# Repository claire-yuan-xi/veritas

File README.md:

# Veritas: A Pill Screener
Veritas is a small owl-shaped pill screener that uses water dissolution and light sensing to check whether an over-the-counter pill matches what the pill's label says.

To use Veritas, first you take a small glass vial of water that is provided alongside Veritas, and then drop the pill inside. Then, you shake the vial for 10 seconds, and then set the vial back inside the owl. If you forget how to do any of these steps, fret not! The OLED screen will walk you through the process. 

Inside, Veritas will first shine five colors of LED (red, green, blue, infrared, and ultraviolet) through the dissolving pill, in that order. Then, a light sensor inside will measure how much of each color makes it through the dissolved pill. These five numbers are the main data points Veritas will send to the mobile app over Bluetooth, which will then start a process of the app comparing the scan of the pill with the known data points of that pill. The mobile app will then send the readings back to the OLED screen, which will then output the result (Math, Doesn't Match, or Inconclusive).
## Why I made Veritas
The WHO estimates that 1 in 10 medical products in low and middle income countries is substandard or falsified. Given the current state of the US' healthcare system, most people have low access to proper lab tests, and when they do, they're often expensive and slow. Most people have no way to check a pill at home.

Owls are known for being wise, which inspired the design of Veritas. Moreover, truth in Latin (and partially Yale's latin motto) inspired the name "Veritas." 

Also, special thanks to my marketing teacher and the friends who helped in the design of Veritas' flyer! Also my access to the school's Adobe Premiere Suite <3

## Features

+ 5 Colors of light shined: red, green, blue, 940 nm infrared, and 400 nm UV
+ TSL2591 high sensitivity light sensor
+ 0.96" OLED screen
+ Seeed XIAO ESP32-S3 with Bluetooth Low Energy 
+ Custom 50 x 40 mm PCB
+ 3D printed 110 mm owl case 
+ USB-C Connection

## Case

The case is a 110 mm sphere with a flat bottom designed in Autodesk Fusion. The case breaks down into 3 parts: 

+ the body with the PCB at the bottom, the cutout for the OLED, the beak, wings, chest feathers, and feet.
+ the chamber for the vial to stand, right above the LEDs, which fits standard sized glass vials (approx. 27 x 60 mm)
+ the roof/sensor cap where the TSL2591 sensor is mounted

The parts are held together with heat-set inserts, to which Im printing in black PLA so as to not let any light in and interfere with the readings.

## PCB

Using KiCad, the PCB ended up being about 50 x 40 mm. The XIAO ESP32-S3 plugs into two 7 pin headers so it can be swapped out whenever. The five LEDs sit in a column under the chamber so their light goes straight up the vial to the sensor. Each LED has its own current-limiting resistor to which the light sensor and the OLED connect with 4 pin headers. 

There's also a spot for a small transistor and diode that could drive a stirring fan, which was left unpopulated for the purposes of Veritas as I found shaking the glass vial by hand works fine. 
The gerbers are in pcb/veritas/gerbers.zip and can be ordered from JLCPCB.

## Schematic

## Firmware
The firmware is in firmware/veritas/veritas.ino and was written in Arduino's desktop IDE. The code essentially covers the commands for the OLED screen display and the Bluetooth connection to the mobile app. 

### Libraries used: 

+ Adafruit TSL2591 library 
+ Adafruit unified sensor 
+ Adafruit SSD1306
+ Adafruit GFX library 
+ ESP32 BLE

## App

The mobile (iPhone) app is written in Swift with SwiftUI (in 'app/'). The app connects Veritas over Bluetooth, starts scans, saves reference scans of the actual, known pills, and compares new scans against them to decide Match, Doesn't Match, or Inconclusive. The app is still a work in progress, which will be finished in tandem with the hardware portion of Veritas.

## Bill of Materials

See [BOM.csv](BOM.csv) for the full list of parts with links and prices. 

## Credits

Component footprints and 3D models are from the standard KiCAD libraries. The XIAO ESP32-S3 model in the renders is a placeholder. 

Libraries by Adafruit(TSL2591, SSD1306, GFX) and Espressif (ESP32 BLE).

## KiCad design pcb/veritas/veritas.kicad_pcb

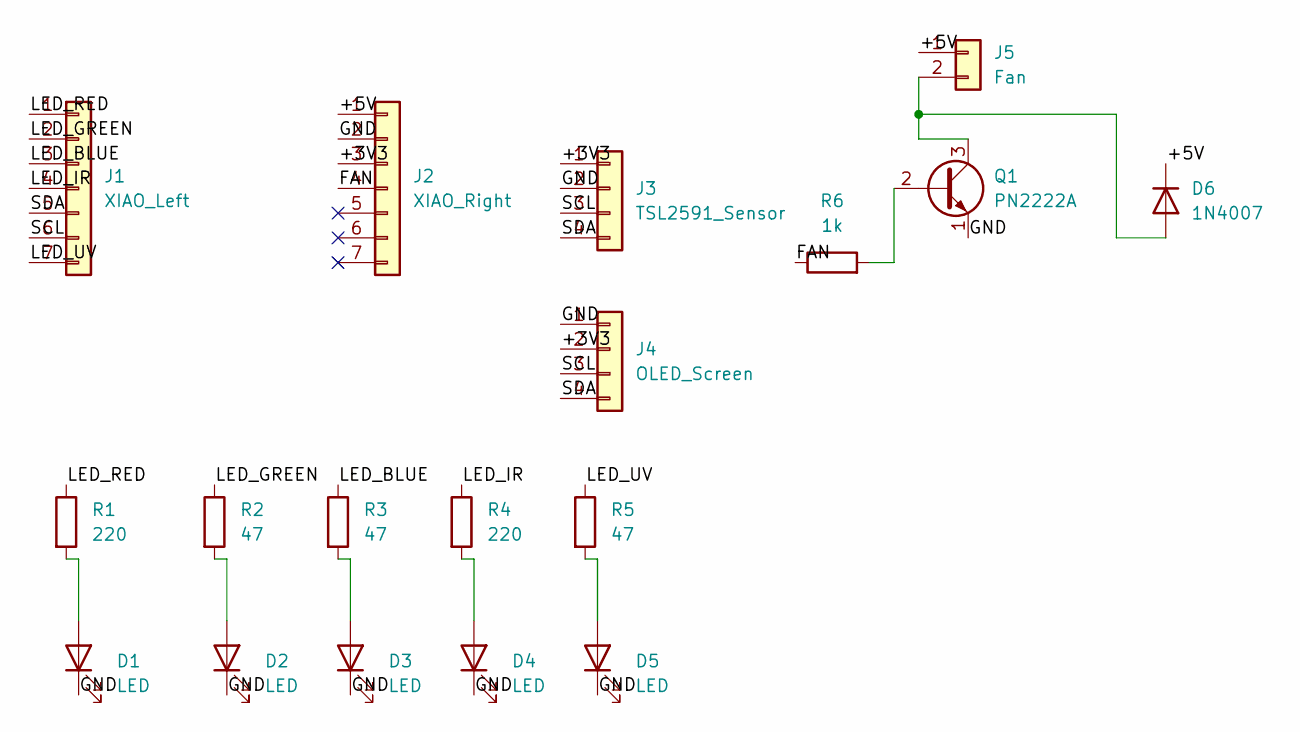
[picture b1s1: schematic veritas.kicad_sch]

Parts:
D1, D2, D3, D4, D5: LED; LED_D5.0mm
D6: 1N4007; D_DO-41_SOD81_P10.16mm_Horizontal
J1: XIAO_Left; PinSocket_1x07_P2.54mm_Vertical
J2: XIAO_Right; PinSocket_1x07_P2.54mm_Vertical
J3: TSL2591_Sensor; PinHeader_1x04_P2.54mm_Vertical
J4: OLED_Screen; PinHeader_1x04_P2.54mm_Vertical
J5: Fan; PinHeader_1x02_P2.54mm_Vertical
Q1: PN2222A; TO-92_Inline
R1, R4: 220; R_Axial_DIN0207_L6.3mm_D2.5mm_P10.16mm_Horizontal
R2, R3, R5: 47; R_Axial_DIN0207_L6.3mm_D2.5mm_P10.16mm_Horizontal
R6: 1k; R_Axial_DIN0207_L6.3mm_D2.5mm_P10.16mm_Horizontal

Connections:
/+3V3: J2.3, J3.1, J4.2
/+5V: D6.1 (K), J2.1, J5.1
/FAN: J2.4, R6.1
/GND: D1.1 (K), D2.1 (K), D3.1 (K), D4.1 (K), D5.1 (K), J2.2, J3.2, J4.1, Q1.1 (E)
/LED_BLUE: J1.3, R3.1
/LED_GREEN: J1.2, R2.1
/LED_IR: J1.4, R4.1
/LED_RED: J1.1, R1.1
/LED_UV: J1.7, R5.1
/SCL: J1.6, J3.3, J4.3
/SDA: J1.5, J3.4, J4.4
unnamed: D1.2 (A), R1.2
unnamed: D2.2 (A), R2.2
unnamed: D3.2 (A), R3.2
unnamed: D4.2 (A), R4.2
unnamed: D5.2 (A), R5.2
unnamed: D6.2 (A), J5.2, Q1.3 (C)
unnamed: Q1.2 (B), R6.2

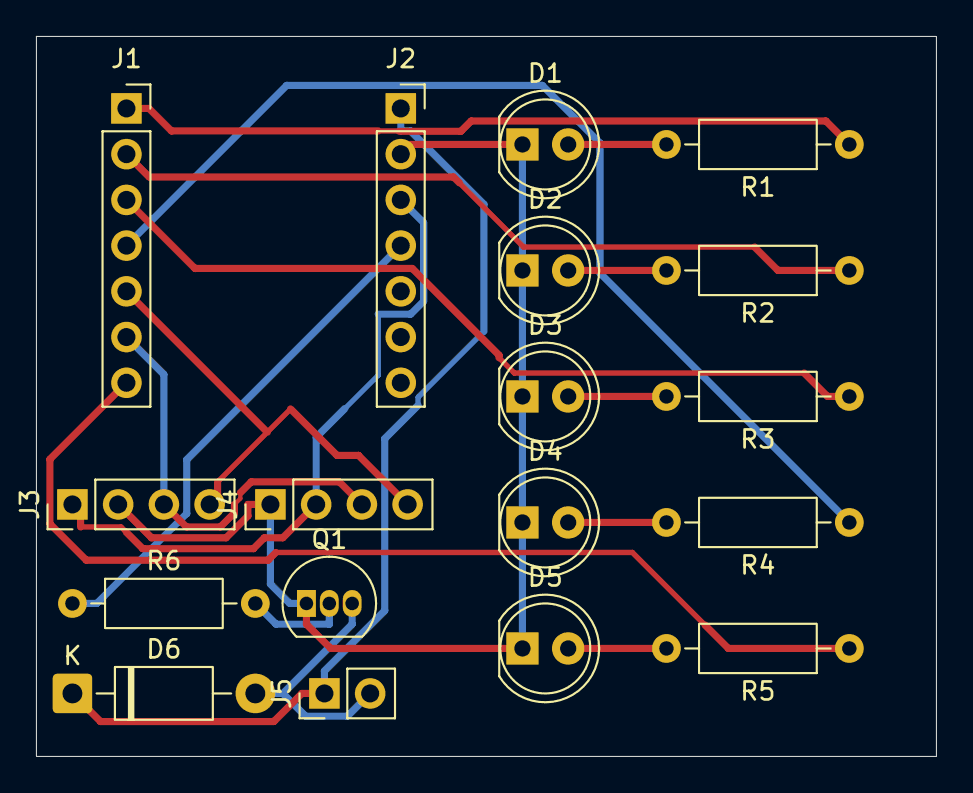
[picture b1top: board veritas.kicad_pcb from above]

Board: 2 copper layers, 50.0 x 40.0 mm, 18 parts (0 on the bottom side), 18 nets.

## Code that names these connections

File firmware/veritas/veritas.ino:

#include <Wire.h>
#include <Adafruit_Sensor.h>
#include <Adafruit_TSL2591.h>
#include <Adafruit_GFX.h>
#include <Adafruit_SSD1306.h>
#include <BLEDevice.h>
#include <BLEServer.h>
#include <BLE2902.h>

// firmware for the Seeed XIAO ESP32-S3

// LED pins (one LED per color of light)
const int LED_RED = D0;
const int LED_GREEN = D1;
const int LED_BLUE = D2;
const int LED_IR = D3;
const int LED_UV = D6;

// fan pin
const int FAN_PIN = D10;

// all LEDs in the order their flashed
const int LEDS[] = {LED_RED, LED_GREEN, LED_BLUE, LED_IR, LED_UV};
const char* LED_NAMES[] = {"red", "green", "blue", "ir", "uv"};
const int NUM_LEDS = 5;

//this is the light sensor above the vial
Adafruit_TSL2591 tsl = Adafruit_TSL2591(2591);

// one reading per LED
uint16_t readings [NUM_LEDS];

// the OLED screen (128 x 64 pixels) i.e. the owls face
Adafruit_SSD1306 display(128, 64, &Wire, -1);

// owl moods (how the eyes look)
const int AWAKE = 0;
const int SLEEPY = 1;
const int HAPPY = 2;
const int WORRIED = 3;
const int UNSURE = 4;
const int BROKEN = 5;
const int LOOK_DOWN = 6;

// where the eyes sit on the screen
const int EYE_L = 36;
const int EYE_R = 92;
const int EYE_Y = 24;
const int EYE_SIZE = 16;

// draws one eye at x in the given mood
void drawEye(int x, int mood) {
  if (mood == BROKEN) {
    // X eye
    for (int t = 0; t< 2; t++) {
      display.drawLine(x-10 + t, EYE_Y - 10, x +10 + t, EYE_Y + 10, SSD1306_WHITE);
      display.drawLine(x-10+t, EYE_Y +10, x+10+t, EYE_Y -10, SSD1306_WHITE);
    }
    return;
  }

  if (mood == HAPPY) {
    // ^ shape: a white circle with a black circle covering its bottom
    display.fillCircle(x, EYE_Y + 4, EYE_SIZE, SSD1306_WHITE);
    display.fillCircle(x, EYE_Y + 12, EYE_SIZE, SSD1306_BLACK);
    return;
  }

  // normal eye: white circle + black pupil
  display.fillCircle(x, EYE_Y, EYE_SIZE, SSD1306_WHITE);
  int pupilY = EYE_Y;
  if (mood == LOOK_DOWN) {
    pupilY = EYE_Y + 7;
  }
  display.fillCircle(x, pupilY, 6, SSD1306_BLACK);

  if (mood == SLEEPY) {
    // eyelid: black box over the top half of the eye
    display.fillRect(x - EYE_SIZE, EYE_Y - EYE_SIZE, EYE_SIZE * 2 + 1, EYE_SIZE, SSD1306_BLACK);
  }
}

// draw both eyes plus a status line at the bottom
void drawOwl(int mood, const char* status) {
  display.clearDisplay();

  if (mood == UNSURE) {
    // one eye open
    drawEye(EYE_L, AWAKE);   
    // one squinty eye
    drawEye(EYE_R, SLEEPY);  
  } else {
    drawEye(EYE_L, mood);
    drawEye(EYE_R, mood);
  }

  if (mood == WORRIED) {
    // eyebrows tilted up in the middle
    display.drawLine(EYE_L - 14, 6, EYE_L + 12, 1, SSD1306_WHITE);
    display.drawLine(EYE_R - 12, 1, EYE_R + 14, 6, SSD1306_WHITE);
  }

  // status text, centered (each letter is 6 pixels wide)
  display.setTextSize(1);
  display.setTextColor(SSD1306_WHITE);
  int textWidth = strlen(status) * 6;
  display.setCursor((128 - textWidth) / 2, 54);
  display.print(status);

  display.display();
}

// show each color's reading as a line of text
void showReadings() {
  display.clearDisplay();
  display.setTextSize(1);
  display.setTextColor(SSD1306_WHITE);
  display.setCursor(0,0);
  display.println("Veritas results");
  for (int i = 0; i < NUM_LEDS; i++) {
    display.print(LED_NAMES[i]);
    display.print(": ");
    display.println(readings[i]);
  }
  display.display();
}

// bluetooth: the names the iPhone app looks for and connects to
#define DEVICE_NAME  "Veritas"
#define SERVICE_UUID "7a1c0001-3f2b-4c8e-9a6d-2b5e8f1c0a01"
// owl --> phone
#define RESULTS_UUID "7a1c0002-3f2b-4c8e-9a6d-2b5e8f1c0a01" 
// phone --> owl 
#define COMMAND_UUID "7a1c0003-3f2b-4c8e-9a6d-2b5e8f1c0a01"  

// where we put the readings for the phone
BLECharacteristic* resultsChar;  
bool phoneConnected = false;
String command = "";             

// runs when the phone connects or disconnects
class ConnectionCallbacks : public BLEServerCallbacks {
  void onConnect(BLEServer* server) {
    phoneConnected = true;
  }
  void onDisconnect(BLEServer* server) {
    phoneConnected = false;
    // let the phone find us again
    BLEDevice::startAdvertising();  
  }
};

// runs when the phone sends a command (like "SCAN")
class CommandCallbacks : public BLECharacteristicCallbacks {
  void onWrite(BLECharacteristic* c) {
    command = c->getValue();
  }
};

// start Bluetooth so the phone can find veritas
void startBluetooth() {
  BLEDevice::init(DEVICE_NAME);
  BLEServer* server = BLEDevice::createServer();
  server->setCallbacks(new ConnectionCallbacks());
  BLEService* service = server->createService(SERVICE_UUID);

  resultsChar = service->createCharacteristic(RESULTS_UUID,
      BLECharacteristic::PROPERTY_READ | BLECharacteristic::PROPERTY_NOTIFY);
  resultsChar->addDescriptor(new BLE2902());

  BLECharacteristic* commandChar = service->createCharacteristic(COMMAND_UUID,
      BLECharacteristic::PROPERTY_WRITE);
  commandChar->setCallbacks(new CommandCallbacks());

  service->start();
  BLEDevice::getAdvertising()->addServiceUUID(SERVICE_UUID);
  BLEDevice::startAdvertising();
}

// turn one LED on, measures the light that gets thru the vial, then turns it off
uint16_t readLED(int i) {
  digitalWrite(LEDS[i], HIGH);
  delay(50);
  uint32_t lum = tsl.getFullLuminosity();
  uint16_t full = lum & 0xFFFF;
  digitalWrite(LEDS[i], LOW);
  delay(100);
  return full;
}

// countdown on the owl while the vial is shaken 
void shakeCountdown() {
  for (int s = 10; s > 0; s--) {
    char msg[20];
    sprintf(msg, "Shake vial %d", s);
    drawOwl(LOOK_DOWN, msg);
    delay(1000);
  }
}

// a test func for shaking countdown
void runScan() {
  shakeCountdown();

  String message = "";
  for (int i = 0; i < NUM_LEDS; i++) {
    // owl looks down at the vial, with a status line and a progress bar
    char msg[24];
    sprintf(msg, "Scanning %s %d/%d", LED_NAMES[i], i + 1, NUM_LEDS);
    drawOwl(LOOK_DOWN, msg);
    display.drawRect(14, 44, 100, 6, SSD1306_WHITE);
    display.fillRect(14, 44, 100 * (i + 1) / NUM_LEDS, 6, SSD1306_WHITE);
    display.display();

    readings[i] = readLED(i);
    Serial.print(LED_NAMES[i]);
    Serial.print(": ");
    Serial.println(readings[i]);

    // build the text "red,green,blue,ir,uv" for the phone
    message += String(readings[i]);
    if (i < NUM_LEDS - 1) {
      message += ",";
    }
  }

  // send the numbers to the phone
  resultsChar->setValue(message);
  resultsChar->notify();
  drawOwl(AWAKE, "Sent! Check phone");
}

void setup() {
  Serial.begin(115200);

  //led outputs and off switches
  for (int i = 0; i < NUM_LEDS; i++) {
    pinMode(LEDS[i], OUTPUT);
    digitalWrite(LEDS[i], LOW);
  }

  pinMode(FAN_PIN, OUTPUT);
  digitalWrite(FAN_PIN, LOW);

  // start the light sensor
  bool sensorOK = tsl.begin();
  if (sensorOK) {
    Serial.println("Light sensor found");
    tsl.setGain(TSL2591_GAIN_MED);
    tsl.setTiming(TSL2591_INTEGRATIONTIME_100MS);
  } else{
    Serial.println("Light sensor NOT found, check wiring");
  }

  // start the OLED screen (address 0x3C); sleepy owl until the phone connects w bluetooth
  if (display.begin(SSD1306_SWITCHCAPVCC, 0x3C)) {
    if (sensorOK) {
      drawOwl(SLEEPY, "Open the Veritas app");
    } else {
      // X eyes
      drawOwl(BROKEN, "Sensor missing");  
    }
  } else {
    Serial.println("Screen NOT found, check wiring");
  }

  startBluetooth();
  Serial.println("Veritas ready");
}

void loop() {
  // The owl reacts when the phone connects or leaves
  static bool wasConnected = false;
  if (phoneConnected != wasConnected) {
    wasConnected = phoneConnected;
    if (phoneConnected) {
      drawOwl(AWAKE, "Connected");
    } else {
      drawOwl(SLEEPY, "Open the Veritas app");
    }
  }

  // for testing without the app: type a command in the Serial Monitor
  if (Serial.available()) {
    command = Serial.readStringUntil('\n');
    command.trim();
  }

  // User performs what the phone (or the Serial Monitor) asked
  if (command == "SCAN") {
    command = "";
    runScan();
  } else if (command == "MATCH") {
    command = "";
    drawOwl(HAPPY, "Match");
  } else if (command == "NOMATCH") {
    command = "";
    drawOwl(WORRIED, "Doesn't match");
  } else if (command == "UNSURE") {
    command = "";
    drawOwl(UNSURE, "Inconclusive ?");
  } else if (command != "") {
    command = "";  
  }

  delay(50);
}
